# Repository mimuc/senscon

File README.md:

# [SensCon: Embedding Physiological Sensing into Virtual Reality Controllers](./chiossi2023senscon.pdf)

This repository contains Unity Project and PPG and EDA data logging system for the Mobile HCI '23 full paper "SensCon: Embedding Physiological Sensing into Virtual Reality Controllers"

# Abstract 
Virtual reality experiences increasingly use physiological data for virtual environment adaptations to evaluate user experience and immersion. Previous research required complex medical-grade equipment to collect physiological data, limiting real-world applicability. To overcome this, we present SensCon for skin conductance and heart rate data acquisition. To identify the optimal sensor location in the controller, we conducted a first study investigating users' controller grasp behavior. In a second study, we evaluated the performance of SensCon against medical-grade devices in six scenarios regarding user experience and signal quality. Users subjectively preferred SensCon in terms of usability and user experience. Moreover, the signal quality evaluation showed satisfactory accuracy across static, dynamic, and cognitive scenarios. Therefore, SensCon reduces the complexity of capturing and adapting the environment via real-time physiological data. By open-sourcing SensCon, we enable researchers and practitioners to adapt their virtual reality environment effortlessly. Finally, we discuss possible use cases for virtual reality-embedded physiological sensing.

Authors: [Francesco Chiossi](https://www.linkedin.com/in/francescochiossi/), [Thomas Kosch](https://thomaskosch.com/), [Luca Menghini](https://www.linkedin.com/in/menghiniluca/), [Steeven Villa](https://posthci.com/) and [Sven Mayer](https://sven-mayer.com/).

DOI: https://doi.org/10.1145/3604270

## Full Paper

The paper is available in [chiossi2023senscon.pdf](./chiossi2023senscon.pdf).

# Application 
- The [./Senscon/](./Senscon) provides Unity scene with the different tasks used for the validation of Senscon. 
- The [./Arduino/](./Arduino) provides the Arduino  code to create the LSL stream from the Arduino Sensors.
- The [./Server/](./Server) provides Python code to receive the LSL stream from the Arduino Sensors.
- The [./Schematics/](./Schematics) provides the SensCon schematics for both EDA and PPG sensors. 

## Materials
We integrated the PPG and EDA sensors into two HTC Vive controllers. 
- For the communication and local sensor control unit, we used an [ESP 8266 D1 Mini](www.openhacks.com/uploadsproductos/tutorial_nb.pdf) microcontroller offering both WiFi and Bluetooth connectivity. 
- We use a [Groove galvanic skin response (GSR) sensor](https://wiki.seeedstudio.com/Grove-GSR_Sensor/) to measure EDA with a sample rate of 192 Hz.
- We use a [Pulse Sensor](https://pulsesensor.com/) for PPG sensing with a sample rate of 50 Hz.

The controllers have built-in batteries with 960mAh at 3.85V. However, this is under the minimum required 4V for the microcontroller. Thus,  we recommend to add a power bank connected to the ESP flash port instead. 

## Contribute

The easiest way to contribute is to provide feedback! We would love to hear what you think. Please write to [francescochiossi93@gmail.com](mailto:francescochiossi93@gmail.com) and [info@sven-mayer.com](mailto:info@sven-mayer.com) for closer communication.

## Licenses and Citation

- The [dataset](./dataset) itself, available in [Creative Commons Public Domain Dedication (CC-0)](https://creativecommons.org/share-your-work/public-domain/cc0/), represented the results from consented anonymous participants and was collected by Francesco Chiossi. 
- The [./Study1/Step01_Image_preprocessing.py](./Study1/Step01_Image_preprocessing.py) provides the code for image perspective transformation.
- The [./Study1/Step02_AreaCalc.py](./Study1/Step02_AreaCalc.py) provides the code for replicating the results from Study 1.
- The [./Study 2/Step1-Results-SensCon.md](./Study%202/Step1-Results-SensCon.md) provides the code for reading the LSL output from SensCon.
- The [./Study 2/Step2-Plots.md](./Study%202/Step2-Plots.md) provides the code for preprocessing and replicating the results and figures from Study 2 in the paper.
- The [./Study 2/Step3-BlandAltman_analyses.md](./Study%202/Step3-BlandAltman_analyses.md) provides the commented code for Bland-Altman analysis.

The contained "source code" (i.e., Python and R scripts and Jupyter Notebooks) of this work is made available under the terms of [GNU GPLv3](./LICENSE). They are fully available also in the [Open Science Framework](https://osf.io/h9mjs/).

Copyright &copy; 2023. [LMU Munich Media Informatics Group](https://www.medien.ifi.lmu.de). All rights reserved.

## Citing the Paper and Application

Below are the BibTex entries to cite the paper and data set.

```
@inproceedings{chiossi2023senscon,
author = {Chiossi, Francesco and Kosch, Thomas and Menghini, Luca, And Villa, Steeven and Mayer, Sven},
title = {{SensCon: Embedding Physiological Sensing into Virtual Reality Controllers}},
year = {2023},
publisher = {Association for Computing Machinery},
address = {New York, NY, USA},
url = {https://doi.org/10.1145/3491102.3517593},
doi = {10.1145/3604270},
volume = {7},
number = {MHCI},
journal = {Proc. ACM Hum.-Comput. Interact.},
pages = {1–32},
numpages = {32},
month = {sep},
articleno = {223},
keywords = {Virtual Reality, Controller, Physiological Computing, Physiological Interaction, Embedded Systems},
}
```

```
@misc{chiossi2023sensconapp,
 author={Chiossi, Francesco and Kosch, Thomas and Menghini, Luca and Vila, Steeven and Mayer, Sven},
  title = {{SensCon: Embedding Physiological Sensing into Virtual Reality Controllers}},
  year = {2023},
  publisher = {OSF},
  journal = {Open Science Framework},
  doi = {10.17605/OSF.IO/H9MJS},
}

```

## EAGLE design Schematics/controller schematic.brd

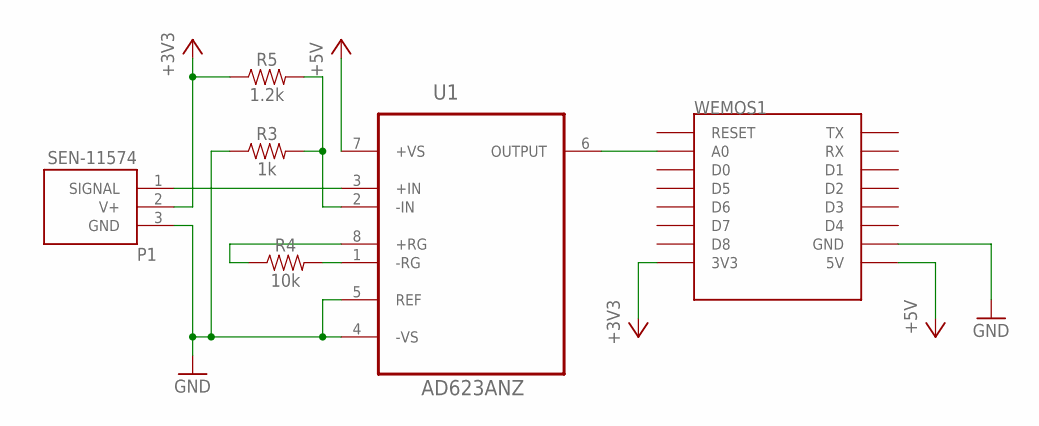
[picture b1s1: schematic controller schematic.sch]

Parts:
P1: SEN-11574; XDCR_SEN-11574
R3: 1k; AXIAL-0.3
R4: 10k; AXIAL-0.3
R5: 1.2k; AXIAL-0.3
U1: AD623ANZ; DIP254P762X533-8
WEMOS1: WEMOS-D1-MINI

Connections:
+3V3: P1.2 (V+), R5.P$1 (1), WEMOS1.3V3
+5V: U1.7 (+VS), WEMOS1.5V
GND: P1.3 (GND), R3.P$1 (1), U1.4 (-VS), U1.5 (REF), WEMOS1.GND
unnamed: P1.1 (SIGNAL), U1.3 (+IN)
unnamed: U1.6 (OUTPUT), WEMOS1.A0
unnamed: R4.P$2 (2), U1.1 (-RG)
unnamed: R4.P$1 (1), U1.8 (+RG)
unnamed: R3.P$2 (2), R5.P$2 (2), U1.2 (-IN)

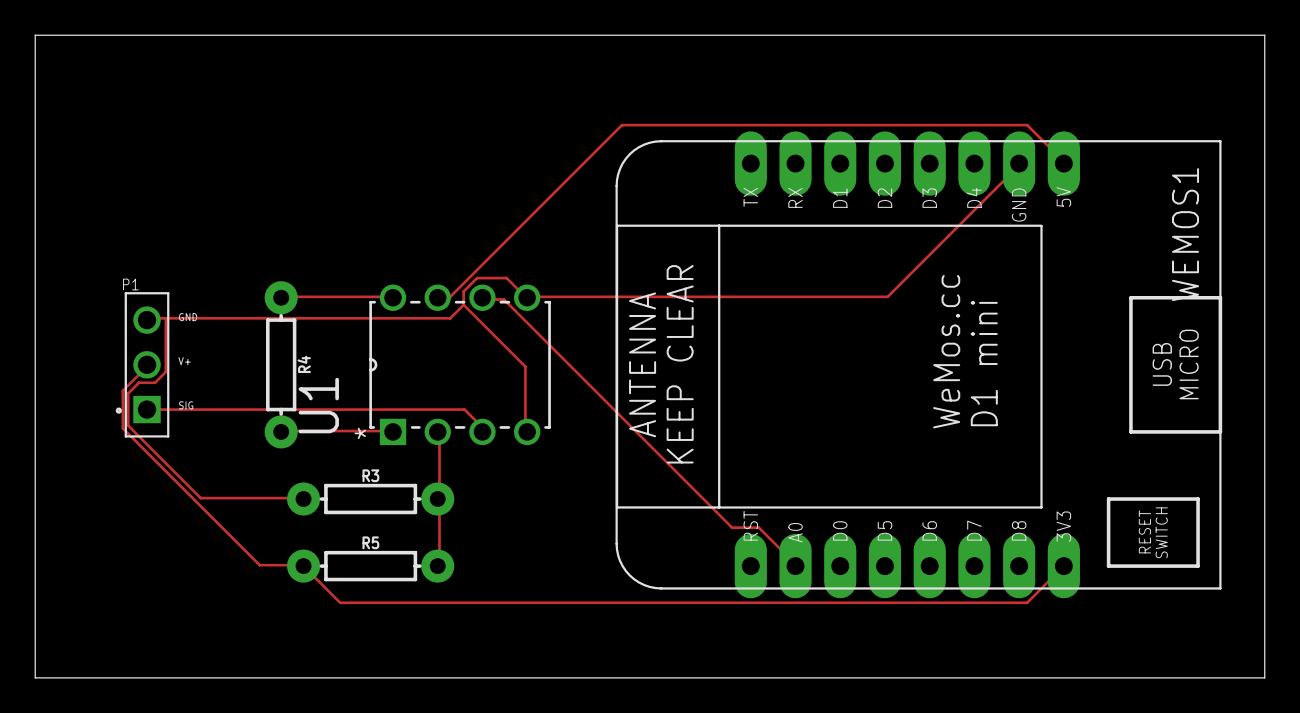
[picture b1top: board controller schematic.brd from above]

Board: 2 copper layers, 69.8 x 36.5 mm, 6 parts (0 on the bottom side), 8 nets.

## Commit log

2022-03-23 init
2022-03-23 Added Arduino and Python Server code
2022-03-24 init gitignore
2022-03-24 init unity
2022-03-27 Fixed compiler bug
2022-03-27 Renamed Project. Added LSL logging for EDA and PPG
2022-03-28 Removed unnecesseary scripts. Removed unnecessary assets
2022-03-28 added blank scene
2022-03-28 Added logging for medical devices
2022-03-31 Fixed logging bug
2022-03-31 Updated data logging logic for medical EDA
2022-04-02 added Stroop Room
2022-04-02 move Stroop Task
2022-04-02 added Stroop Languages
2022-04-02 removed old files
2022-04-02 update Stroop
2022-04-02 Stroop running
2022-04-02 added Selection Task
2022-04-02 update n back
2022-04-02 adjustments
2022-04-03 Changed LSL script
2022-04-03 Fixed bugs, modified logging mechanism
2022-04-03 Added printout script
2022-04-04 Controller working in N-Back, not In stroop yet
2022-04-04 update Stroop to work with two controller
2022-04-04 Revert "Merge branch 'main' of github.com:mimuc/Physens-VRcontroller"
    This reverts commit f777bf66d2a0e6f24cfc65d88d8cdb3fd75988ac, reversing
    changes made to fb66eb24288077e570590a396b615839df6fa5e6.
2022-04-04 adding back LaserPointer ClickState
2022-04-04 fucked up
2022-04-04 added Manual XR manager
2022-04-04 changed height of appearance of items in the selection task
2022-08-15 New sensor data logging
2022-09-08 Fixed bugs in Arduino and Python scripts
2022-09-08 Commented out weird except block
2022-09-08 fun with thomas
2022-09-09 update ports, set PPG at 250Hz
2022-10-24 Last changes
2022-10-25 Performance logged (finalized)
2023-06-11 add senscon pics
2023-06-12 Added Study 1, Step 01
2023-06-12 Create controller schematic.s#1
2023-06-12 Added Schematic files
2023-06-12 Added Step1_Results.html
2023-06-12 Update deleted scripts
2023-06-12 Added BA Analysis code
2023-06-12 Rename Step3-BlandAltman_analyses.Rmd to Step3-BlandAltman_analyses.md
2023-06-12 Create Study2

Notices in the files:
parts and their libraries:
SparkFun-Resistors: Licensing: Creative Commons ShareAlike 4.0 International - https://creativecommons.org/licenses/by-sa/4.0
